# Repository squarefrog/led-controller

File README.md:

# LED Controller PCB

This repository contains a schematic and board layout for a WS2812B control board, based around the [Adafruit Huzzah Breakout](https://www.adafruit.com/product/2471) ESP8266 module.

The [Eagle](https://www.autodesk.com/products/eagle/overview) design files can be found in the `design` directory.

## Parts List

| Schematic Symbol | Description                   | Part Number              |
|------------------|-------------------------------|--------------------------|
| J1               | 5V 5A DC Barrel Jack          | Cliff DC10A / DC10L      |
| J2               | 3.5mm pitch terminal block    | CamdenBoss CTBP3051/3    |
| R1               | 150Ω Resistor                 | 0805 SMD package         |
| C1               | 3300µF Electrolytic Capacitor | 7.5mm lead pitch         |
| U$1              | Adafruit Huzzah Breakout      | Adafruit product ID 2471 |

I recommend you use 2x10 female pin headers with 2.54mm pitch to allow you to remove the [Adafruit Huzzah](https://www.adafruit.com/product/2471) without de-soldering.  Additionally, you may use 4x M2.5 screws to mount the PCB.

## Schematic

## Layout

## Gerbers

Pre-generated Gerber files are available in the `gerbers` directory. This will let you upload them to your preferred PCB fabricator to get a PCB made.

## Software

For the software, please see the [software repository](https://github.com/squarefrog/led-controller-software).

## License

Cern OHL v1.2. See [LICENSE](LICENSE) file.

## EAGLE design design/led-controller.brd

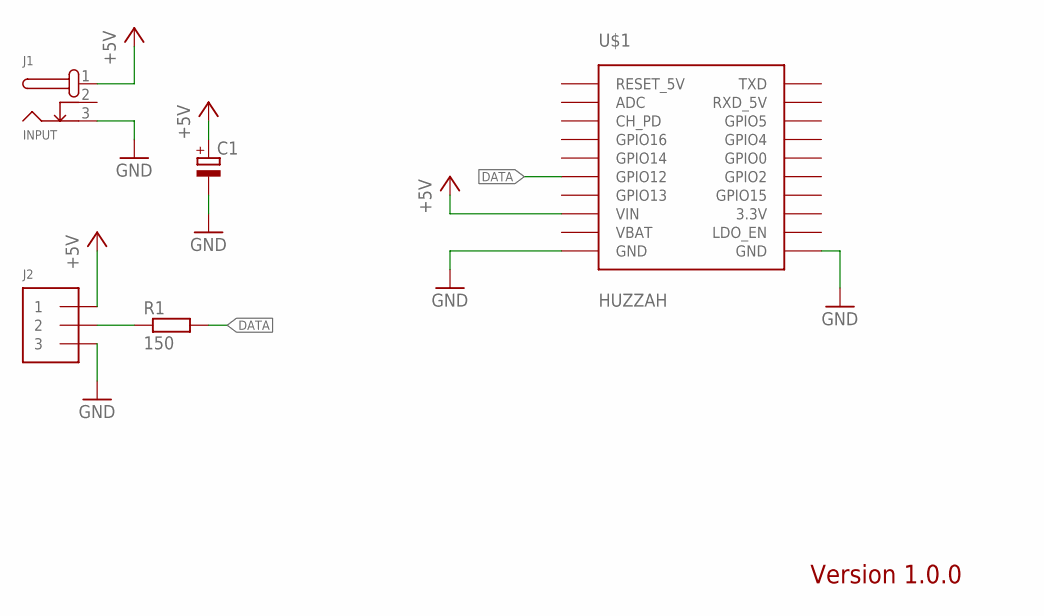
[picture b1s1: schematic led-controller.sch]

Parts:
C1: CPOL-EUE7.5-16; E7,5-16
J1: INPUT; DC10
J2: 3,5MM-1X3-TERMBLOCK
R1: 150; R1206W
U$1: HUZZAH

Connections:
2: J1.2
+5V: C1.+, J1.1, J2.1, U$1.VIN
DATA: R1.2, U$1.GPIO12
DOUT: J2.2, R1.1
GND: C1.-, J1.3, J2.3, U$1.GND@1 (GND), U$1.GND@2 (GND)

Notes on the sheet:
Version 1.0.0

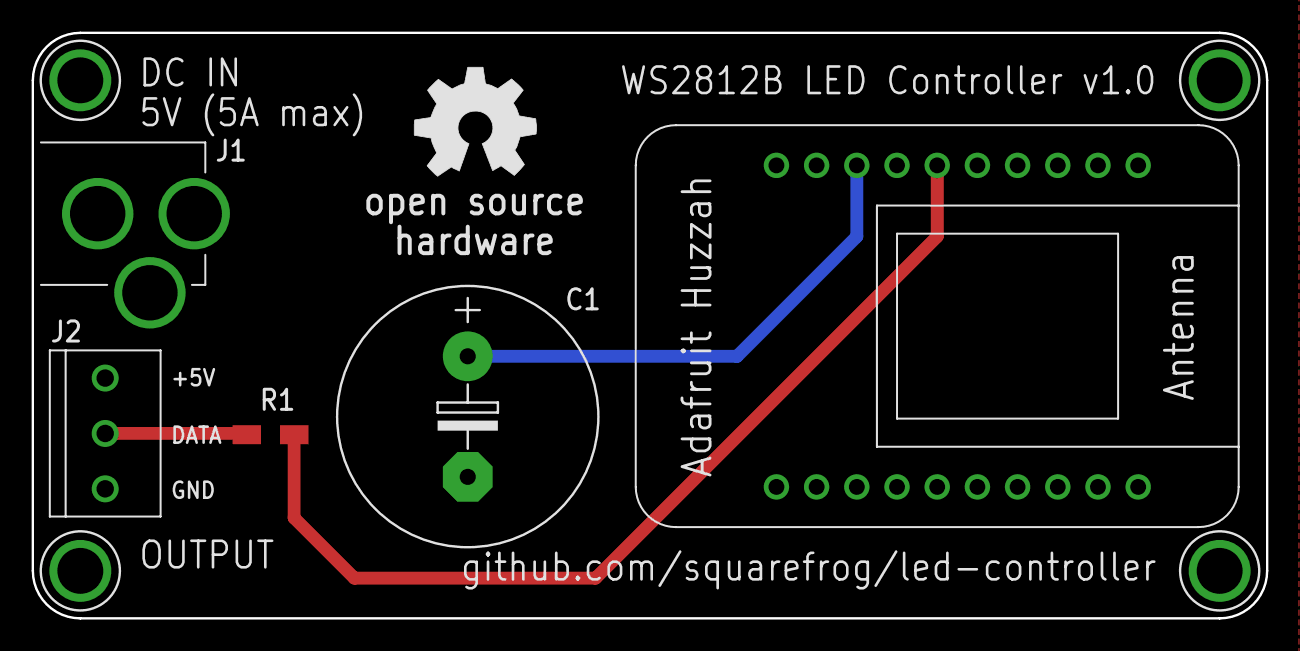
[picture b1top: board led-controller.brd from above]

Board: 2 copper layers, 78.0 x 37.0 mm, 6 parts (0 on the bottom side), 4 nets.

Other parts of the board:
U$2: OSHW_8MM

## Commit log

2018-04-11 Update README image links
2018-04-11 Cleanup README parts table
2018-04-13 Add missing width dimension to board
